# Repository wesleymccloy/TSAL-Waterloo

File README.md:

#TSAL Waterloo

##Welcome to my repository

This is where I am currently keeping my EAGLE files for the UW Electric Motor-sports Student Design Team Tractive System Active Light

###Look at the pictures of the PCB and schematic!

##Credit to:

> **Marc-Andre Vaillancourt**: *Circuit detecteur de haute tension pour une voiture electrique* (2011)
> [A link to the report](https://code.google.com/p/tsalivd/)

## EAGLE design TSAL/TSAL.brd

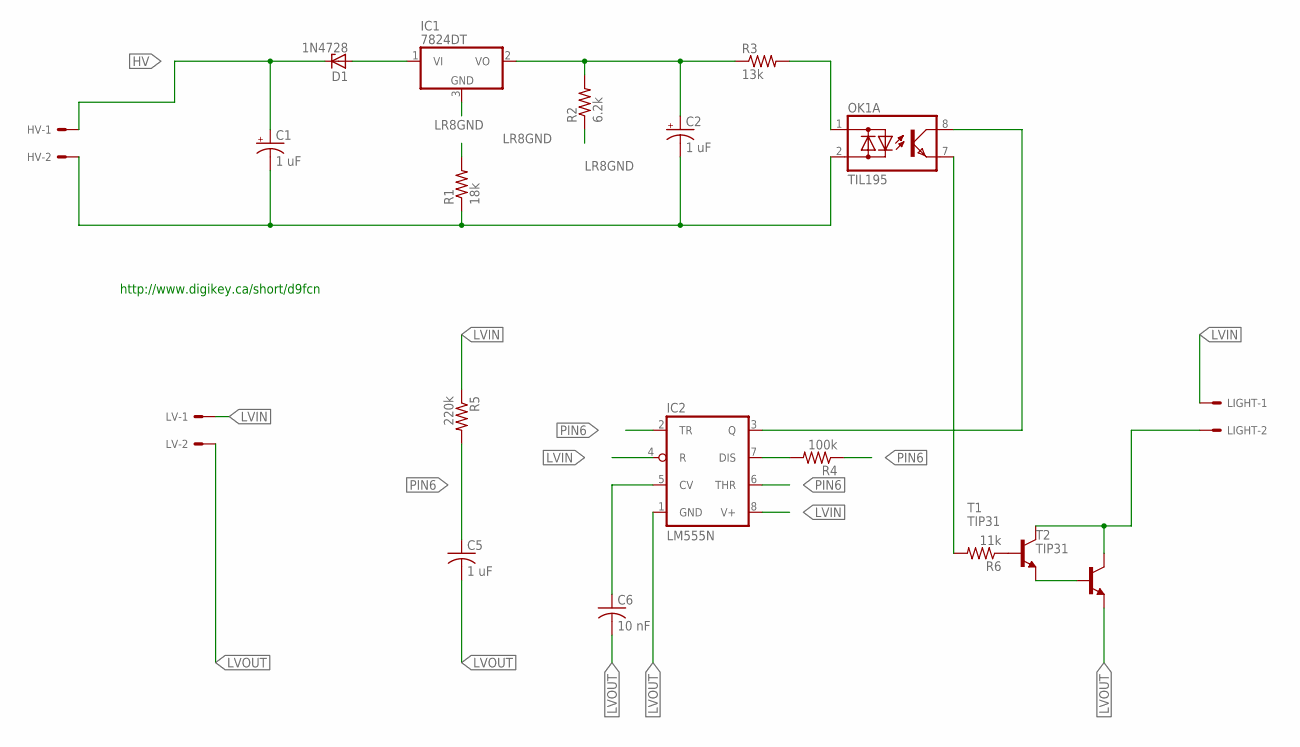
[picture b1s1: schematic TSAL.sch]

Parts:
C1, C2: 1 uF; E2,5-7
C5: 1 uF; C050-035X075
C6: 10 nF; C025-025X050
D1: 1N4728; DO41Z10
HV: KK-156-2
IC1: 7824DT; TO252
IC2: LM555N; DIL08-ROUND
LIGHT: KK-156-2
LV: KK-156-2
OK1: TIL195; DIL08
R1: 18k; 0617/22
R2: 6.2k; 0617/22
R3: 13k; 0617/17
R4: 100k; 0207/7
R5: 220k; 0207/7
R6: 11k; 0411/12
T1, T2: TIP31; TO220

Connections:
HV: C1.+, D1.C, HV.1
LR8GND: IC1.3 (GND), R1.2, R2.1
LVIN: IC2.4 (R), IC2.8 (V+), LIGHT.1, LV.1, R5.1
LVOUT: C5.2, C6.2, IC2.1 (GND), LV.2, T2.3 (E)
unnamed: D1.A, IC1.1 (VI)
unnamed: C2.+, IC1.2 (VO), R2.2, R3.1
unnamed: C1.-, C2.-, HV.2, OK1.2 (AC2), R1.1
unnamed: IC2.7 (DIS), R4.2
unnamed: LIGHT.2, T1.2 (C), T2.2 (C)
unnamed: T1.3 (E), T2.1 (B)
unnamed: OK1.1 (AC1), R3.2
unnamed: C6.1, IC2.5 (CV)
unnamed: IC2.3 (Q), OK1.8 (C)
unnamed: OK1.7 (E), R6.2
unnamed: R6.1, T1.1 (B)
PIN6: C5.1, IC2.2 (TR), IC2.6 (THR), R4.1, R5.2

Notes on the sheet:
http://www.digikey.ca/short/d9fcn

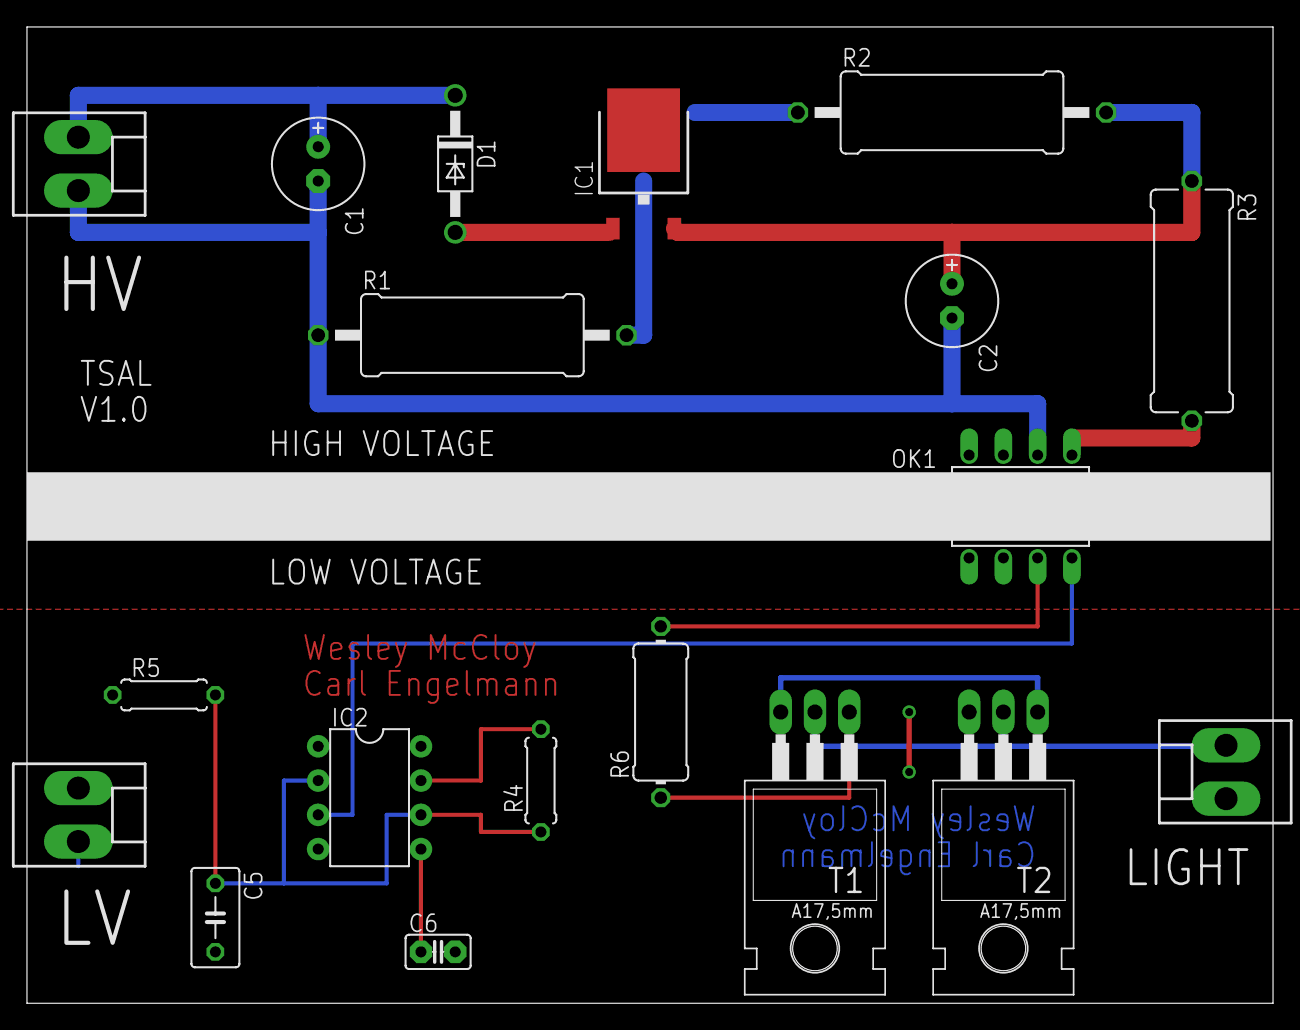
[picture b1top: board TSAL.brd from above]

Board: 2 copper layers, 92.4 x 72.4 mm, 19 parts (0 on the bottom side), 16 nets.

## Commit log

2014-07-31 trying again, initial commit
2014-07-31 added test-file
2014-07-31 new TSAL files
2014-08-01 Updating README.md
2014-08-01 second readme update
2014-08-01 Create gh-pages branch via GitHub
2014-08-01 added Wiki thing in README.md
2014-08-01 minor change README
2014-08-01 shit, so many
2014-09-22 pictures
2014-09-22 readme change
